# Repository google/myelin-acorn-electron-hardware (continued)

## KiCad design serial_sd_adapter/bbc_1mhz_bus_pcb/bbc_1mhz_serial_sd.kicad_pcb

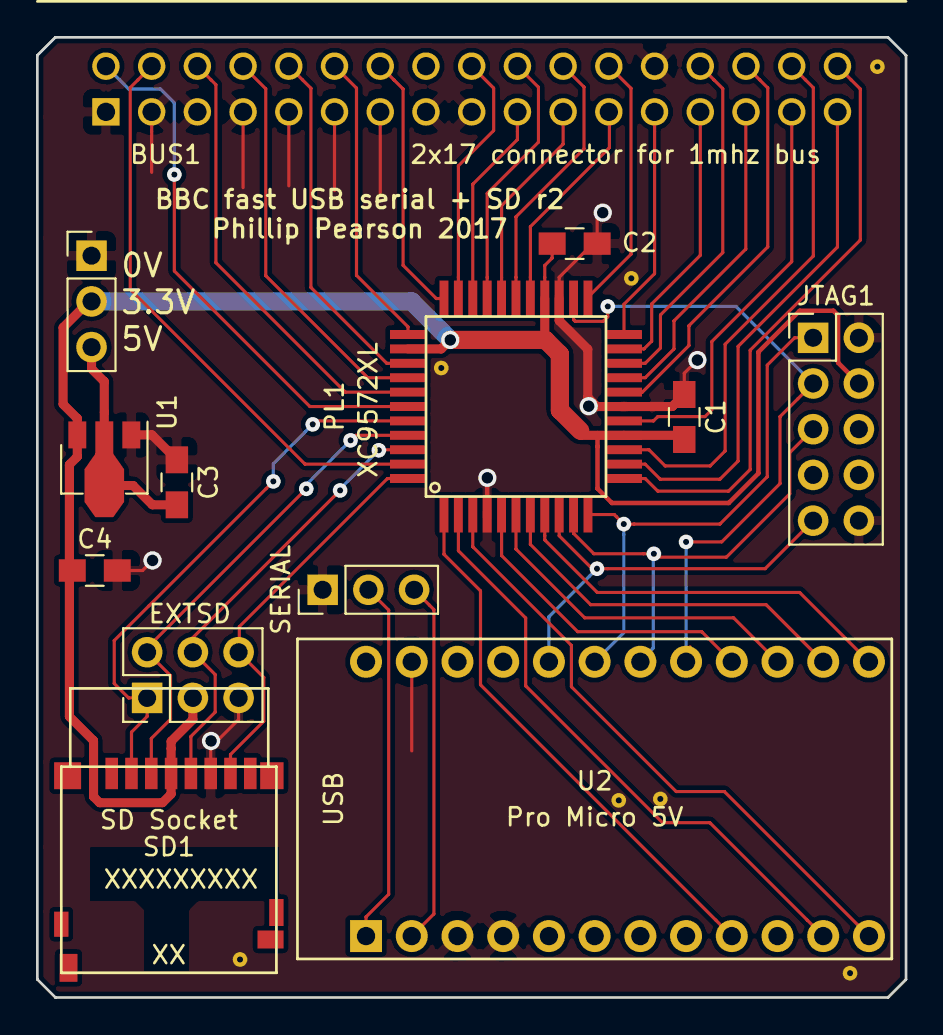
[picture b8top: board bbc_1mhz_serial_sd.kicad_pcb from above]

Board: 2 copper layers, 48.3 x 53.3 mm, 20 parts (0 on the bottom side), 43 nets.

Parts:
BUS1: 2x17 connector for 1mhz bus; bbc_1mhz_bus_board
C1, C2: 100n; C_0805_HandSoldering
C3, C4: 1u; C_0805_HandSoldering
EXTPWR: ext pwr; Pin_Header_Straight_1x03_Pitch2.54mm
EXTSD: ext sd; Pin_Header_Straight_2x03_Pitch2.54mm
JTAG1: jtag; Pin_Header_Straight_2x05_Pitch2.54mm
PL1: XC9572XL; xilinx_vqg44
SD1: SD Socket; hirose_micro_sd_card_socket
SERIAL: serial; Pin_Header_Straight_1x03_Pitch2.54mm
U1: MCP1700T-3302E/MB; SOT-89-3
U2: Pro Micro 5V; pro_micro
staple_single1, staple_single2, staple_single3, staple_single4, staple_single5, staple_single6, staple_single7: via_single

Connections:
3V3: C1.2, C2.1, C4.1, EXTPWR.2, EXTSD.3, JTAG1.4, PL1.15, PL1.26, PL1.35, SD1.4, U1.3
5V: C3.2, EXTPWR.3, U1.2
GND: BUS1.1, BUS1.3, BUS1.5, BUS1.7, BUS1.9, BUS1.11, BUS1.13, BUS1.15, BUS1.17, BUS1.26, C1.1, C2.2, C3.1, C4.2, EXTPWR.1, EXTSD.5, JTAG1.2, JTAG1.10, PL1.4, PL1.17, PL1.25, SD1.6, SERIAL.1, U1.1, U2.3, U2.4, U2.23, staple_single1.1, staple_single2.1, staple_single3.1, staple_single4.1, staple_single5.1, staple_single6.1, staple_single7.1
avr_INT: PL1.8, U2.13
avr_MISC1: PL1.1, U2.9
avr_MISO: PL1.6, U2.15
avr_MOSI: PL1.7, U2.14
avr_RXD: SERIAL.3, U2.2
avr_SCK: PL1.5, U2.16
avr_TXD: SERIAL.2, U2.1
avr_nSD_SEL: PL1.2, U2.11
avr_nSS: PL1.3, U2.12
bbc_1MHZE: BUS1.4, PL1.43
bbc_A0: BUS1.27, PL1.21
bbc_A1: BUS1.28, PL1.20
bbc_A2: BUS1.29, PL1.19
bbc_A3: BUS1.30, PL1.18
bbc_A4: BUS1.31, PL1.16
bbc_A5: BUS1.32, PL1.14
bbc_A6: BUS1.33, PL1.13
bbc_A7: BUS1.34, PL1.12
bbc_D0: BUS1.18, PL1.32
bbc_D1: BUS1.19, PL1.31
bbc_D2: BUS1.20, PL1.30
bbc_D3: BUS1.21, PL1.29
bbc_D4: BUS1.22, PL1.28
bbc_D5: BUS1.23, PL1.27
bbc_D6: BUS1.24, PL1.23
bbc_D7: BUS1.25, PL1.22
bbc_RnW: BUS1.2, PL1.39
bbc_nIRQ: BUS1.8, PL1.37
bbc_nNMI: BUS1.6, PL1.38
bbc_nPGFC: BUS1.10, PL1.36
bbc_nPGFD: BUS1.12, PL1.34
bbc_nRESET: BUS1.14, PL1.33
cpld_TCK: JTAG1.1, PL1.11, U2.19
cpld_TDI: JTAG1.9, PL1.9, U2.20
cpld_TDO: JTAG1.3, PL1.24, U2.17
cpld_TMS: JTAG1.5, PL1.10, U2.18
sd_MISO: EXTSD.6, PL1.44, SD1.7
sd_MOSI: EXTSD.2, PL1.41, SD1.3
sd_SCK: EXTSD.4, PL1.42, SD1.5
sd_nSS: EXTSD.1, PL1.40, SD1.2

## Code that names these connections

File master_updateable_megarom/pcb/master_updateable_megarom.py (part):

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        # we could wire flash_nCE low and ignore bbc_nCE.
        Pin(1,  "P2.10",   ["D6"]),
        Pin(2,  "GTS2",    ["D7"]),
        Pin(4,  "P2.12",   ["bbc_A0"]),
        Pin(5,  "GTS1",    ["bbc_A1"]),
        Pin(6,  "P2.15",   ["bbc_A2"]),
        Pin(7,  "P2.17",   ["bbc_A3"]),
        Pin(8,  "P1.2",    ["bbc_A10"]),
        Pin(9,  "P1.5",    ["bbc_A4"]),
        Pin(10, "P1.6",    ["bbc_A16"]),
        Pin(11, "P1.8",    ["bbc_A5"]),
        Pin(12, "P1.3",    ["bbc_A11"]),
        Pin(13, "P1.4",    ["bbc_A6"]),
        Pin(15, "P1.GCK1", ["bbc_A9"]),  # Should have put SCK on one of these!
        Pin(16, "P1.GCK2", ["bbc_A7"]),  # Try drilling out one of the tracks and
        Pin(17, "P1.GCK3", ["bbc_A8"]),  # using it as a spare GCK pin.
        Pin(18, "P1.10",   ["bbc_A12"]),
        Pin(19, "P1.15",   ["cpld_JP1"]),  # TODO(r2) shuffle pins around so
        Pin(20, "P1.17",   ["bbc_A15"]),   # cpld_SCK ends up on a GCK.
        Pin(22, "P3.2",    ["cpld_JP0"]),
        Pin(23, "P1.12",   ["bbc_A13"]),
        Pin(24, "P3.5",    ["bbc_A14"]),
        Pin(25, "P3.8",    ["cpld_MISO"]),
        Pin(27, "P3.9",    ["cpld_MOSI"]),
        Pin(31, "P3.3",    ["cpld_SCK"]),
        Pin(32, "P3.4",    ["cpld_SS"]),
        Pin(33, "P3.11",   ["flash_A0"]),
        Pin(34, "P3.6",    ["flash_A1"]),
        Pin(35, "P3.14",   ["flash_A2"]),
        Pin(36, "P3.15",   ["flash_A3"]),
        Pin(38, "P3.17",   ["flash_A4"]),
        Pin(39, "P3.10",   ["flash_A5"]),
        Pin(40, "P3.12",   ["flash_A6"]),
        Pin(42, "P3.16",   ["flash_A7"]),
        Pin(43, "P4.2",    ["flash_A12"]),
        Pin(44, "P4.5",    ["flash_A15"]),
        Pin(45, "P4.8",    ["flash_A16"]),
        Pin(46, "P4.3",    ["flash_A18"]),
        Pin(47, "P4.4",    ["flash_nWE"]),
        Pin(48, "P4.11",   ["flash_A17"]),
        Pin(49, "P4.6",    ["flash_A14"]),
        Pin(50, "P4.14",   ["flash_A13"]),
        Pin(51, "P4.10",   ["flash_A8"]),
        Pin(52, "P4.12",   ["flash_A9"]),
        Pin(56, "P4.15",   ["flash_A11"]),
        Pin(57, "P4.17",   ["flash_nOE"]),
        Pin(58, "P2.3",    ["flash_A10"]),
        Pin(59, "P2.4",    ["D0"]),
        Pin(60, "P2.2",    ["D2"]),
        Pin(61, "P2.5",    ["D3"]),
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        Pin(55, "VCCIO_2V5_3V3", ["3V3"]),

        # 4 JTAG programming interface pins
        Pin(28, "TDI", ["cpld_TDI"]),
        Pin(29, "TMS", ["cpld_TMS"]),
        Pin(30, "TCK", ["cpld_TCK"]),
        Pin(53, "TDO", ["cpld_TDO"]),
    ],
)
cpld_cap1 = myelin_kicad_pcb.C0805("100n", "3V3", "GND", ref="C1")
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    value="jtag",
    desc="2x5 header for JTAG programming.  Use generic 0.1 inch header strip or Digikey ED1543-ND.",
    pins=[
        Pin(1, "TCK", ["cpld_TCK"]), # top left
        Pin(2, "GND", ["GND"]), # top right
        Pin(3, "TDO", ["cpld_TDO"]),
        Pin(4, "3V3", ["3V3"]),
        Pin(5, "TMS", ["cpld_TMS"]),
        Pin(6, "NC"),
        Pin(7, "NC"),
        Pin(8, "NC"),
        Pin(9, "TDI", ["cpld_TDI"]),
        Pin(10, "GND", ["GND"]),
    ],
)
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    desc="1x3 0.1 inch male header",
    pins=[
        Pin(1, "GND", ["GND"]),
        Pin(2, "SCK", ["cpld_SCK"]),
        Pin(3, "nSS", ["cpld_SS"]),
        Pin(4, "MISO", ["cpld_MOSI"]),
        Pin(5, "MOSI", ["cpld_MISO"]),
    ],
)

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    desc="1x4 0.1 inch male header",
    pins=[
        Pin(1, "GND", ["GND"]),
        Pin(2, "JP0", ["cpld_JP0"]),
        Pin(3, "JP1", ["cpld_JP1"]),
        Pin(4, "3V3", ["5V"]),
    ],
)
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    value="SST39SF010A/020A/040",
    desc="128kB/256kB/512kB flash chip in SST 'NH' PLCC-32 package: SST39SF040-XX-XX-NHE, SST39SF020A-XX-XX-NHE, or SST39SF010A-XX-XX-NHE",
    pins=[
        Pin(1, "A18",  ["flash_A18"]),
        Pin(2, "A16",  ["flash_A16"]),
        Pin(3, "A15",  ["flash_A15"]),
        Pin(4, "A12",  ["flash_A12"]),
        Pin(5, "A7",   ["flash_A7"]),
        Pin(6, "A6",   ["flash_A6"]),
        Pin(7, "A5",   ["flash_A5"]),
        Pin(8, "A4",   ["flash_A4"]),
        Pin(9, "A3",   ["flash_A3"]),
        Pin(10, "A2",  ["flash_A2"]),
        Pin(11, "A1",  ["flash_A1"]),
        Pin(12, "A0",  ["flash_A0"]),
        Pin(13, "D0",  ["D0"]),
        Pin(14, "D1",  ["D1"]),
        Pin(15, "D2",  ["D2"]),
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        Pin(20, "D6",  ["D6"]),
        Pin(21, "D7",  ["D7"]),
        Pin(22, "nCE", ["GND"]),  # flash chip permanently enabled
        Pin(23, "A10", ["flash_A10"]),
        Pin(24, "nOE", ["flash_nOE"]),
        Pin(25, "A11", ["flash_A11"]),
        Pin(26, "A9",  ["flash_A9"]),
        Pin(27, "A8",  ["flash_A8"]),
        Pin(28, "A13", ["flash_A13"]),
        Pin(29, "A14", ["flash_A14"]),
        Pin(30, "A17", ["flash_A17"]),
        Pin(31, "nWE", ["flash_nWE"]),
        Pin(32, "VDD", ["5V"]),
    ],
)
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    value="MOS ROM",
    desc="Adapter to emulate a 600mil 28-pin DIP, e.g. Digikey 1175-1525-5-ND",
    pins=[
        Pin( "1", "A15", ["bbc_A15"]),
        Pin( "2", "A12", ["bbc_A12"]),
        Pin( "3", "A7",  ["bbc_A7"]),
        Pin( "4", "A6",  ["bbc_A6"]),
        Pin( "5", "A5",  ["bbc_A5"]),
        Pin( "6", "A4",  ["bbc_A4"]),
        Pin( "7", "A3",  ["bbc_A3"]),
        Pin( "8", "A2",  ["bbc_A2"]),
        Pin( "9", "A1",  ["bbc_A1"]),
        Pin("10", "A0",  ["bbc_A0"]),
        Pin("11", "D0",  ["D0"]),
        Pin("12", "D1",  ["D1"]),
        Pin("13", "D2",  ["D2"]),
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        Pin("17", "D5",  ["D5"]),
        Pin("18", "D6",  ["D6"]),
        Pin("19", "D7",  ["D7"]),
        Pin("20", "nCS", ),  # bbc /CS ignored because it's tied to GND on the motherboard
        Pin("21", "A10", ["bbc_A10"]),
        Pin("22", "A16", ["bbc_A16"]),
        Pin("23", "A11", ["bbc_A11"]),
        Pin("24", "A9",  ["bbc_A9"]),
        Pin("25", "A8",  ["bbc_A8"]),
        Pin("26", "A13", ["bbc_A13"]),
        Pin("27", "A14", ["bbc_A14"]),
        Pin("28", "VCC", ["5V"]),
    ],
)
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#     value="74LVC245",
#     pins=[
#         Pin( 1, "A->B", ["abuf_ext_to_cpu"]),
#         Pin( 2, "A0", ["ext_A0"]),
#         Pin( 3, "A1", ["ext_A1"]),
#         Pin( 4, "A2", ["ext_A2"]),
#         Pin( 5, "A3", ["ext_A3"]),
#         Pin( 6, "A4", ["ext_A4"]),
#         Pin( 7, "A5", ["ext_A5"]),
#         Pin( 8, "A6", ["ext_A6"]),
#         Pin( 9, "A7", ["ext_A7"]),
#         Pin(10, "GND", ["GND"]),
#         Pin(11, "B7", ["cpu_A7"]),
#         Pin(12, "B6", ["cpu_A6"]),
#         Pin(13, "B5", ["cpu_A5"]),
#         Pin(14, "B4", ["cpu_A4"]),
#         Pin(15, "B3", ["cpu_A3"]),
#         Pin(16, "B2", ["cpu_A2"]),
#         Pin(17, "B1", ["cpu_A1"]),
#         Pin(18, "B0", ["cpu_A0"]),
#         Pin(19, "nCE", ["abuf_nCE"]),
#         Pin(20, "VCC", ["3V3"]),
#     ],
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#     value="74LVC245",
#     pins=[
#         Pin( 1, "A->B", ["abuf_ext_to_cpu"]),
#         Pin( 2, "A0", ["ext_A8"]),
#         Pin( 3, "A1", ["ext_A9"]),
#         Pin( 4, "A2", ["ext_A10"]),
#         Pin( 5, "A3", ["ext_A11"]),
#         Pin( 6, "A4", ["ext_A12"]),
#         Pin( 7, "A5", ["ext_A13"]),
#         Pin( 8, "A6", ["ext_A14"]),
#         Pin( 9, "A7", ["ext_A15"]),
#         Pin(10, "GND", ["GND"]),
#         Pin(11, "B7", ["cpu_A15_2"]),
#         Pin(12, "B6", ["cpu_A14_2"]),
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#         Pin(29, "P0.5",   [""]),
#         Pin(30, "P0.6",   [""]),
#         Pin(31, "P0.7",   [""]),
#         Pin(32, "nRESET", ["mcu_nreset"]),
#         Pin(33, "VCCD",   ["mcu_vccd"]),  # regulated supply; connect to 1uF cap or 1.8V
#         Pin(34, "VDDD",   ["5V"]),
#         Pin(35, "VDDA",   ["5V"]),
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
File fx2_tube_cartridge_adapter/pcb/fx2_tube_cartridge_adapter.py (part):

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        # front of cartridge / bottom layer of PCB
        Pin( "B1", "5V",    "5V"),
        Pin( "B2", "A10"),
        Pin( "B3", "D3",    "cpu_D3"),
        Pin( "B4", "A11"),
        Pin( "B5", "A9"),
        Pin( "B6", "D7",    "cpu_D7"),
        Pin( "B7", "D6",    "cpu_D6"),
        Pin( "B8", "D5",    "cpu_D5"),
        Pin( "B9", "D4",    "cpu_D4"),
        Pin("B10", "nOE2"),
        Pin("B11", "BA7",   "cpu_A7"),
        Pin("B12", "BA6",   "cpu_A6"),
        Pin("B13", "BA5",   "cpu_A5"),
        Pin("B14", "BA4",   "cpu_A4"),
        Pin("B15", "BA3",   "cpu_A3"),
        Pin("B16", "BA2",   "cpu_A2"),
        Pin("B17", "BA1",   "cpu_A1"),
        Pin("B18", "BA0",   "cpu_A0"),
        Pin("B19", "D0",    "cpu_D0"),
        Pin("B20", "D2",    "cpu_D2"),
        Pin("B21", "D1",    "cpu_D1"),
        Pin("B22", "GND",   "GND"),
        # rear of cartridge / top layer of PCB
        Pin( "A1", "5V",    "5V"),
        Pin( "A2", "nOE"),
        Pin( "A3", "nRST",  "cpu_nRST"),
        # A4 is RnW on the Elk, and on the master for &FCxx, so it's safe to use
        # this for the Tube, but not for the logic analyzer.
        Pin( "A4", "RnW",   "cpu_RnW"),
        Pin( "A5", "A8"),
        Pin( "A6", "A13"),
        Pin( "A7", "A12"),
        Pin( "A8", "PHI0",  "cpu_CLK"),
        Pin( "A9", "-5V"),
        Pin("A10", "NC"),
        Pin("A11", "READY", "elk_READY_master_RnW"),
        Pin("A12", "nNMI",  "cpu_nNMI"),
        Pin("A13", "nIRQ",  "cpu_nIRQ"),
        Pin("A14", "nINFC", "elk_nINFC"),
        Pin("A15", "nINFD"),
        Pin("A16", "ROMQA"),
        Pin("A17", "16MHZ", "elk_16MHz"),
        Pin("A18", "nROMSTB"),
        Pin("A19", "ADOUT"),
        Pin("A20", "ADGND"),
        Pin("A21", "ADIN"),
        Pin("A22", "GND",   "GND"),
    ],
)
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    value="tube",
    pins=[
        Pin( 1, "0V", "GND"),
        Pin( 2, "RnW", "cpu_RnW"),
        Pin( 3, "0V", "GND"),
        Pin( 4, "2MHzE", "cpu_CLK"),
        Pin( 5, "0V", "GND"),
        Pin( 6, "/IRQ", "cpu_nIRQ"),
        Pin( 7, "0V", "GND"),
        Pin( 8, "/TUBE", "bbc_nTUBE"),
        Pin( 9, "0V", "GND"),
        Pin(10, "/RST", "cpu_nRST"),
        Pin(11, "0V", "GND"),
        Pin(12, "D0", "cpu_D0"),
        Pin(13, "0V", "GND"),
        Pin(14, "D1", "cpu_D1"),
        Pin(15, "0V", "GND"),
        Pin(16, "D2", "cpu_D2"),
        Pin(17, "0V", "GND"),
        Pin(18, "D3", "cpu_D3"),
        Pin(19, "0V", "GND"),
        Pin(20, "D4", "cpu_D4"),
        Pin(21, "0V", "GND"),
        Pin(22, "D5", "cpu_D5"),
        Pin(23, "0V", "GND"),
        Pin(24, "D6", "cpu_D6"),
        Pin(25, "0V", "GND"),
        Pin(26, "D7", "cpu_D7"),
        Pin(27, "0V", "GND"),
        Pin(28, "A0", "cpu_A0"),
        Pin(29, "0V", "GND"),
        Pin(30, "A1", "cpu_A1"),
        Pin(31, "+5V", "5V"),
        Pin(32, "A2", "cpu_A2"),
        Pin(33, "+5V", "5V"),
        Pin(34, "A3", "cpu_A3"),
        Pin(35, "+5V", "5V"),
        Pin(36, "A4", "cpu_A4"),
        Pin(37, "+5V", "5V"),
        Pin(38, "A5", "cpu_A5"),
        Pin(39, "+5V", "5V"),
        Pin(40, "A6", "cpu_A6"),
    ],
)

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    value="XC9572XL",
    buses=["cpu_D", "tube_D"],
    pins=[
        Pin(39, "P1.2", "cpu_D4"),
        Pin(40, "P1.5", "cpu_D5"),
        Pin(41, "P1.6", "cpu_D6"),
        Pin(42, "P1.8", "elk_nINFC"),
        Pin(43, "P1.9-GCK1", "cpu_D7"),
        Pin(44, "P1.11-GCK2", "cpu_A0"),
        Pin( 1, "P1.14-GCK3", "elk_16MHz"),
        Pin( 2, "P1.15", "cpu_A1"),
        Pin( 3, "P1.17", "cpu_A2"),
        Pin( 4, "GND", "GND"),
        Pin( 5, "P3.2", "cpu_A4"),
        Pin( 6, "P3.5", "cpu_A5"),
        Pin( 7, "P3.8", "cpu_A6"),
        Pin( 8, "P3.9", "tube_CLK"),
        Pin( 9, "TDI", "cpld_TDI"),
        Pin(10, "TMS", "cpld_TMS"),
        Pin(11, "TCK", "cpld_TCK"),
        Pin(12, "P3.11", "tube_D0"),
        Pin(13, "P3.14", "tube_D3"),
        Pin(14, "P3.15", "tube_D1"),
        Pin(15, "VCCINT_3V3", "3V3"),
        Pin(16, "P3.17", "tube_D7"),
        Pin(17, "GND", "GND"),
        Pin(18, "P3.16", "tube_D2"),
        Pin(19, "P4.2", "tube_D6"),
        Pin(20, "P4.5", "tube_D4"),
        Pin(21, "P4.8", "tube_D5"),
        Pin(22, "P4.11", "tube_A0"),
        Pin(23, "P4.14", "tube_nTUBE"),
        Pin(24, "TDO", "cpld_TDO"),
        Pin(25, "GND", "GND"),
        Pin(26, "VCCIO_2V5_3V3", "3V3"),
        Pin(27, "P4.15", "tube_RnW"),
        Pin(28, "P4.17", "tube_A2"),
        Pin(29, "P2.2", "tube_A1"),
        Pin(30, "P2.5", "cpu_RnW"),
        Pin(31, "P2.6", "cpu_CLK"),
        Pin(32, "P2.8", "bbc_nTUBE"),
        Pin(33, "P2.9-GSR", "cpu_D0"),
        Pin(34, "P2.11-GTS2", "cpu_D1"),
        Pin(35, "VCCINT_3V3", "3V3"),
        Pin(36, "P2.14-GTS1", "cpu_A7"),
        Pin(37, "P2.15", "cpu_D2"),
        Pin(38, "P2.17", "cpu_D3"),
    ],
)
cpld_cap1 = myelin_kicad_pcb.C0805("100n", "3V3", "GND", ref="C1", handsoldering=False)
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	pins=[
		Pin(1, "3V3", "3V3_PI"),  # for when we want the Pi to power the CPLD
		Pin(2, "5V"),
		Pin(3, "GPIO0-2", ["tube_A1"]),
		Pin(4, "5V"),
		Pin(5, "GPIO1-3", ["tube_A2"]),
		Pin(6, "ser_GND", ["pi_serial_GND"]),
		Pin(7, "GPIO4", ["tube_nRST"]),
		Pin(8, "ser_TX", ["pi_serial_TX"]),
		Pin(9, "GND", ["GND"]),
		Pin(10, "ser_RX", ["pi_serial_RX"]),
		Pin(11, "GPIO17", ["tube_nTUBE"]),
		Pin(12, "GPIO18", ["tube_RnW"]),
		Pin(13, "GPIO21-27", ["tube_A0"]),
		Pin(14, "GND", ["GND"]),
		Pin(15, "GPIO22", ["tube_D4"]),
		Pin(16, "GPIO23", ["tube_D5"]),
		Pin(17, "3V3"),
		Pin(18, "GPIO24", ["tube_D6"]),
		Pin(19, "GPIO10", ["tube_D2"]),
		Pin(20, "GND", ["GND"]),
		Pin(21, "GPIO9", ["tube_D1"]),
		Pin(22, "GPIO25", ["tube_D7"]),
		Pin(23, "GPIO11", ["tube_D3"]),
		Pin(24, "GPIO8", ["tube_D0"]),
		Pin(25, "GND", ["GND"]),
		Pin(26, "GPIO7", ["tube_CLK"]),
	],
)

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	identifier="SERIAL1",  # TODO(r2) rename to SERIAL
	value="Pi Serial",
	pins=[
		Pin(1, "GND", ["pi_serial_GND"]),
		Pin(2, "TX", ["pi_serial_TX"]),
		Pin(3, "RX", ["pi_serial_RX"]),
	],
)

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    identifier="JTAG1",  # TODO(r2) rename to JTAG
    value="jtag",
    pins=[
        Pin(1, "TCK", ["cpld_TCK"]), # top left
        Pin(2, "GND", ["GND"]), # top right
        Pin(3, "TDO", ["cpld_TDO"]),
        Pin(4, "3V3", ["3V3"]),
        Pin(5, "TMS", ["cpld_TMS"]),
        Pin(6, "NC"),
        Pin(7, "NC"),
        Pin(8, "NC"),
        Pin(9, "TDI", ["cpld_TDI"]),
        Pin(10, "GND", ["GND"]),
    ],
)
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    pins=[
        # left side, top to bottom, left to right, with board face up
        # and USB socket upward
        Pin( "L1", "PD5", "cpu_nNMI"),  # DONE add header for BBC test clip
        Pin( "L2", "PD6", "cpu_nRST"),
        Pin( "L3", "PD7", "tube_A0"),
        Pin( "L4", "GND", "GND"),
        Pin( "L5", "CLK"),
        Pin( "L6", "GND", "GND"),
        Pin( "L7", "RDY0", "analyzer_RDY0"),  # tie to 3V3 via 1k resistor
        Pin( "L8", "RDY1", "tube_CLK_jumper"),  # via jumper to tube_CLK
        Pin( "L9", "GND", "GND"),
        Pin("L10", "GND", "GND"),
        Pin("L11", "GND", "GND"),
        Pin("L12", "FCLK"),
        Pin("L13", "SCL"),
        Pin("L14", "SDA"),
        Pin("L15", "PB0", "tube_D0"),
        Pin("L16", "PB1", "tube_D1"),
        Pin("L17", "PB2", "tube_D2"),
        Pin("L18", "PB3", "tube_D3"),
        Pin("L19", "3V3", "3V3_FX2"),  # generated from USB
        Pin("L20", "3V3", "3V3_FX2"),  # generated from USB

        # right side, top to bottom, left to right
        Pin( "R1", "PD4", "cpu_nIRQ"),
        Pin( "R2", "PD3", "tube_CLK"),
        Pin( "R3", "PD2", "analyzer_PD2_READY"),  # DONE add header for BBC test clip
        Pin( "R4", "PD1", "cpu_SYNC"),  # DONE add header for test clip
        Pin( "R5", "PD0", "analyzer_PD0_RnW"),  # DONE add header to switch Elk pin A4/Master pin A11
        Pin( "R6", "PA7"),
        Pin( "R7", "PA6", "analyzer_PA6"),  # tie to 3V3 via 1k resistor
        Pin( "R8", "PA5", "analyzer_PA5"),  # tie to 3V3 via 1k resistor
        Pin( "R9", "PA4", "analyzer_PA4"),  # tie to GND via 1k resistor
        Pin("R10", "PA3"),
        Pin("R11", "PA2", "analyzer_PA2"),  # tie to 3V3 via 1k resistor
        Pin("R12", "PA1"),
        Pin("R13", "PA0"),
        Pin("R14", "CTL2"),
        Pin("R15", "CTL1"),
        Pin("R16", "CTL0"),
        Pin("R17", "PB7", "tube_D7"),
        Pin("R18", "PB6", "tube_D6"),
        Pin("R19", "PB5", "tube_D5"),
        Pin("R20", "PB4", "tube_D4"),
    ],
)
pull_resistors = [
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# Master: test clip for READY, elk_READY_master_RnW, cpu_nNMI, test clip for SYNC

# L8: capture clock
# L1/PD5/nNMI: 1-pin header (already connected for Elk/Master)
# R4/PD1/SYNC: 1-pin header
# R3/PD2/READY 2-pin header: bridge for Elk, add lead for everyone else
#   [PD2] [elk_READY_master_RnW]
# R5/PD0/RnW: 3-pin header: bridge left for Elk/Beeb, up for Master
#   [tube_RnW] [PD0]

sync_clk_jumper = myelin_kicad_pcb.Component(
	footprint="Pin_Headers:Pin_Header_Straight_2x04_Pitch2.54mm",
	identifier="LEADS",  # TODO(r2) rename to OPTS
	value="Options",
	pins=[
		Pin(1, "", "tube_CLK"),
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
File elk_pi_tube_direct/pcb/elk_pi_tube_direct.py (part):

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    value="edge connector",
    pins=[
        # front of cartridge / bottom layer of PCB
        Pin("B1", "5V", ["elk_5V"]),
        Pin("B2", "A10"),
        Pin("B3", "D3", ["elk_D3"]),
        Pin("B4", "A11"),
        Pin("B5", "A9"),
        Pin("B6", "D7", ["elk_D7"]),
        Pin("B7", "D6", ["elk_D6"]),
        Pin("B8", "D5", ["elk_D5"]),
        Pin("B9", "D4", ["elk_D4"]),
        Pin("B10", "nOE2"),
        Pin("B11", "BA7", ["elk_A7"]),
        Pin("B12", "BA6", ["elk_A6"]),
        Pin("B13", "BA5", ["elk_A5"]),
        Pin("B14", "BA4", ["elk_A4"]),
        Pin("B15", "BA3"),
        Pin("B16", "BA2", ["elk_A2"]),
        Pin("B17", "BA1", ["elk_A1"]),
        Pin("B18", "BA0", ["elk_A0"]),
        Pin("B19", "D0", ["elk_D0"]),
        Pin("B20", "D2", ["elk_D2"]),
        Pin("B21", "D1", ["elk_D1"]),
        Pin("B22", "GND", ["GND"]),
        # rear of cartridge / top layer of PCB
        Pin("A1", "5V", ["elk_5V"]),
        Pin("A2", "nOE"),
        Pin("A3", "nRST", ["elk_nRST"]),
        Pin("A4", "RnW", ["elk_RnW"]),
        Pin("A5", "A8"),
        Pin("A6", "A13"),
        Pin("A7", "A12"),
        Pin("A8", "PHI0", ["elk_PHI0"]),
        Pin("A9", "-5V"),
        Pin("A10", "NC"),
        Pin("A11", "nRDY"),
        Pin("A12", "nNMI"),
        Pin("A13", "nIRQ"),
        Pin("A14", "nINFC", ["elk_nINFC"]),
        Pin("A15", "nINFD"),
        Pin("A16", "ROMQA"),
        Pin("A17", "16MHZ"),
        Pin("A18", "nROMSTB"),
        Pin("A19", "ADOUT"),
        Pin("A20", "ADGND"),
        Pin("A21", "ADIN"),
        Pin("A22", "GND", ["GND"]),
    ],
)
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	pins=[
		Pin(1, "3V3", ["3V3"]),
		Pin(2, "5V", ["5V"]),
		Pin(3, "GPIO0-2", ["tube_A1"]),
		Pin(4, "5V", ["5V"]),
		Pin(5, "GPIO1-3", ["tube_A2"]),
		Pin(6, "ser_GND", ["pi_serial_GND"]),
		Pin(7, "GPIO4", ["tube_nRST"]),
		Pin(8, "ser_TX", ["pi_serial_TX"]),
		Pin(9, "GND", ["GND"]),
		Pin(10, "ser_RX", ["pi_serial_RX"]),
		Pin(11, "GPIO17", ["tube_nTUBE"]),
		Pin(12, "GPIO18", ["tube_RnW"]),
		Pin(13, "GPIO21-27", ["tube_A0"]),
		Pin(14, "GND", ["GND"]),
		Pin(15, "GPIO22", ["tube_D4"]),
		Pin(16, "GPIO23", ["tube_D5"]),
		Pin(17, "3V3", ["3V3"]),
		Pin(18, "GPIO24", ["tube_D6"]),
		Pin(19, "GPIO10", ["tube_D2"]),
		Pin(20, "GND", ["GND"]),
		Pin(21, "GPIO9", ["tube_D1"]),
		Pin(22, "GPIO25", ["tube_D7"]),
		Pin(23, "GPIO11", ["tube_D3"]),
		Pin(24, "GPIO8", ["tube_D0"]),
		Pin(25, "GND", ["GND"]),
		Pin(26, "GPIO7", ["tube_PHI0"]),
	],
)

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	identifier="SERIAL1",
	value="Pi Serial",
	pins=[
		Pin(1, "GND", ["pi_serial_GND"]),
		Pin(2, "TX", ["pi_serial_TX"]),
		Pin(3, "RX", ["pi_serial_RX"]),
	],
)

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    footprint="myelin-kicad:xilinx_vqg44",
    identifier="PL1",
    value="XC9572XL",
    # Prefixes used by update_xilinx_constraints to turn pin names like elk_D0 into
    # signal IDs like elk_D<0> in constraints.ucf:
    buses=["elk_D", "tube_D"],
    pins=[
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        # ninfc brown
        # rnw red

        # NET LED2 LOC = P34; # tube_RnW
        # NET LED3 LOC = P33; # tube_nTUBE
        # NET LED4 LOC = P32; # tube_A0
        # NET LED5 LOC = P31; # tube_D5

        Pin(39, "P1.2", ["elk_D3"]),
        Pin(40, "P1.5", ["elk_nRST"]),
        Pin(41, "P1.6", ["elk_RnW"]),
        Pin(42, "P1.8", ["elk_D7"]),
        Pin(43, "P1.9-GCK1", ["elk_D6"]),
        Pin(44, "P1.11-GCK2", ["elk_D5"]),
        Pin(1, "P1.14-GCK3", ["elk_PHI0"]),
        Pin(2, "P1.15", ["elk_D4"]),
        Pin(3, "P1.17", ["elk_A7"]),
        Pin(4, "GND", ["GND"]),
        Pin(5, "P3.2", ["elk_A6"]),
        Pin(6, "P3.5", ["elk_A5"]),
        Pin(7, "P3.8", ["elk_A4"]),
        Pin(8, "P3.9", ["elk_nINFC"]),
        Pin(9, "TDI", ["cpld_TDI"]),
        Pin(10, "TMS", ["cpld_TMS"]),
        Pin(11, "TCK", ["cpld_TCK"]),
        Pin(12, "P3.11", ["elk_A2"]),
        Pin(13, "P3.14", ["elk_A1"]),
        Pin(14, "P3.15", ["elk_A0"]),
        Pin(15, "VCCINT_3V3", ["3V3"]),
        Pin(16, "P3.17", ["elk_D0"]),
        Pin(17, "GND", ["GND"]),
        Pin(18, "P3.16", ["elk_D2"]),
        Pin(19, "P4.2", ["elk_D1"]),
        Pin(20, "P4.5", ["tube_PHI0"]),
        Pin(21, "P4.8", ["tube_D3"]),
        Pin(22, "P4.11", ["tube_D0"]),
        Pin(23, "P4.14", ["tube_D1"]),
        Pin(24, "TDO", ["cpld_TDO"]),
        Pin(25, "GND", ["GND"]),
        Pin(26, "VCCIO_2V5_3V3", ["3V3"]),
        Pin(27, "P4.15", ["tube_D7"]),
        Pin(28, "P4.17", ["tube_D2"]),
        Pin(29, "P2.2", ["tube_D6"]),
        Pin(30, "P2.5", ["tube_D4"]),
        Pin(31, "P2.6", ["tube_D5"]),
        Pin(32, "P2.8", ["tube_A0"]),
        Pin(33, "P2.9-GSR", ["tube_nTUBE"]),
        Pin(34, "P2.11-GTS2", ["tube_RnW"]),
        Pin(35, "VCCINT_3V3", ["3V3"]),
        Pin(36, "P2.14-GTS1", ["tube_nRST"]),
        Pin(37, "P2.15", ["tube_A2"]),
        Pin(38, "P2.17", ["tube_A1"]),
    ],
)
cpld_cap1 = myelin_kicad_pcb.C0805("100n", "3V3", "GND", ref="C1")
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    identifier="JTAG1",
    value="jtag",
    pins=[
        Pin(1, "TCK", ["cpld_TCK"]), # top left
        Pin(2, "GND", ["GND"]), # top right
        Pin(3, "TDO", ["cpld_TDO"]),
        Pin(4, "3V3", ["3V3"]),
        Pin(5, "TMS", ["cpld_TMS"]),
        Pin(6, "NC"),
        Pin(7, "NC"),
        Pin(8, "NC"),
        Pin(9, "TDI", ["cpld_TDI"]),
        Pin(10, "GND", ["GND"]),
    ],
)
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    value="Elk-Pi 5V",
    pins=[
        Pin(1, "A", ["5V"]),
        Pin(2, "B", ["elk_5V"]),
    ],
)

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
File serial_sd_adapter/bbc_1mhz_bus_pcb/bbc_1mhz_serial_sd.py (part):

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        # want a pure GPIO board.

        Pin("1", "GND", ["GND"]),
        Pin("2", "RnW", ["bbc_RnW"]),
        Pin("3", "GND", ["GND"]),
        Pin("4", "1MHZE", ["bbc_1MHZE"]),
        Pin("5", "GND", ["GND"]),
        Pin("6", "nNMI", ["bbc_nNMI"]),
        Pin("7", "GND", ["GND"]),
        Pin("8", "nIRQ", ["bbc_nIRQ"]),
        Pin("9", "GND", ["GND"]),
        Pin("10", "nPGFC", ["bbc_nPGFC"]),
        Pin("11", "GND", ["GND"]),
        Pin("12", "nPGFD", ["bbc_nPGFD"]),
        Pin("13", "GND", ["GND"]),
        Pin("14", "nRESET", ["bbc_nRESET"]),
        Pin("15", "GND", ["GND"]),
        Pin("16", "AUDIO_IN_OUT"),
        Pin("17", "GND", ["GND"]),
        Pin("18", "D0", ["bbc_D0"]),
        Pin("19", "D1", ["bbc_D1"]),
        Pin("20", "D2", ["bbc_D2"]),
        Pin("21", "D3", ["bbc_D3"]),
        Pin("22", "D4", ["bbc_D4"]),
        Pin("23", "D5", ["bbc_D5"]),
        Pin("24", "D6", ["bbc_D6"]),
        Pin("25", "D7", ["bbc_D7"]),
        Pin("26", "GND", ["GND"]),
        Pin("27", "A0", ["bbc_A0"]),
        Pin("28", "A1", ["bbc_A1"]),
        Pin("29", "A2", ["bbc_A2"]),
        Pin("30", "A3", ["bbc_A3"]),
        Pin("31", "A4", ["bbc_A4"]),
        Pin("32", "A5", ["bbc_A5"]),
        Pin("33", "A6", ["bbc_A6"]),
        Pin("34", "A7", ["bbc_A7"]),
    ],
)

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    footprint="myelin-kicad:xilinx_vqg44",
    identifier="PL1",
    value="XC9572XL",
    # Prefixes used by update_xilinx_constraints to turn pin names like elk_D0 into
    # signal IDs like elk_D<0> in constraints.ucf:
    buses=["bbc_D", "bbc_A"],
    pins=[
        Pin(39, "P1.2", ["bbc_RnW"]),
        Pin(40, "P1.5", ["sd_nSS"]),
        Pin(41, "P1.6", ["sd_MOSI"]),
        Pin(42, "P1.8", ["sd_SCK"]),
        Pin(43, "P1.9-GCK1", ["bbc_1MHZE"]),
        Pin(44, "P1.11-GCK2", ["sd_MISO"]),
        Pin(1, "P1.14-GCK3", ["avr_MISC1"]),
        Pin(2, "P1.15", ["avr_nSD_SEL"]),
        Pin(3, "P1.17", ["avr_nSS"]),
        Pin(4, "GND", ["GND"]),
        Pin(5, "P3.2", ["avr_SCK"]),
        Pin(6, "P3.5", ["avr_MISO"]),
        Pin(7, "P3.8", ["avr_MOSI"]),
        Pin(8, "P3.9", ["avr_INT"]),
        Pin(9, "TDI", ["cpld_TDI"]),
        Pin(10, "TMS", ["cpld_TMS"]),
        Pin(11, "TCK", ["cpld_TCK"]),
        Pin(12, "P3.11", ["bbc_A7"]),
        Pin(13, "P3.14", ["bbc_A6"]),
        Pin(14, "P3.15", ["bbc_A5"]),
        Pin(15, "VCCINT_3V3", ["3V3"]),
        Pin(16, "P3.17", ["bbc_A4"]),
        Pin(17, "GND", ["GND"]),
        Pin(18, "P3.16", ["bbc_A3"]),
        Pin(19, "P4.2", ["bbc_A2"]),
        Pin(20, "P4.5", ["bbc_A1"]),
        Pin(21, "P4.8", ["bbc_A0"]),
        Pin(22, "P4.11", ["bbc_D7"]),
        Pin(23, "P4.14", ["bbc_D6"]),
        Pin(24, "TDO", ["cpld_TDO"]),
        Pin(25, "GND", ["GND"]),
        Pin(26, "VCCIO_2V5_3V3", ["3V3"]),
        Pin(27, "P4.15", ["bbc_D5"]),
        Pin(28, "P4.17", ["bbc_D4"]),
        Pin(29, "P2.2", ["bbc_D3"]),
        Pin(30, "P2.5", ["bbc_D2"]),
        Pin(31, "P2.6", ["bbc_D1"]),
        Pin(32, "P2.8", ["bbc_D0"]),
        Pin(33, "P2.9-GSR", ["bbc_nRESET"]),
        Pin(34, "P2.11-GTS2", ["bbc_nPGFD"]),
        Pin(35, "VCCINT_3V3", ["3V3"]),
        Pin(36, "P2.14-GTS1", ["bbc_nPGFC"]),
        Pin(37, "P2.15", ["bbc_nIRQ"]),
        Pin(38, "P2.17", ["bbc_nNMI"]),
    ],
)
cpld_cap1 = myelin_kicad_pcb.C0805("100n", "GND", "3V3", ref="C1")
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    identifier="JTAG1",
    value="jtag",
    pins=[
        Pin(1, "TCK", ["cpld_TCK"]), # top left
        Pin(2, "GND", ["GND"]), # top right
        Pin(3, "TDO", ["cpld_TDO"]),
        Pin(4, "3V3", ["3V3"]),
        Pin(5, "TMS", ["cpld_TMS"]),
        Pin(6, "NC"),
        Pin(7, "NC"),
        Pin(8, "NC"),
        Pin(9, "TDI", ["cpld_TDI"]),
        Pin(10, "GND", ["GND"]),
    ],
)
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    value="serial",
    pins=[
        Pin(1, "GND", ["GND"]),
        Pin(2, "TX", ["avr_TXD"]),
        Pin(3, "RX", ["avr_RXD"]),
    ],
)

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    value="Pro Micro 5V",
    pins=[
        # two rows of 12 pins, counter clockwise with pin 1 at top left
        Pin(1, "D1_TX_PD3", ["avr_TXD"]),
        Pin(2, "D0_RX_PD2", ["avr_RXD"]),
        Pin(3, "GND", ["GND"]),
        Pin(4, "GND", ["GND"]),
        Pin(5, "D2_SDA_PD1"),
        Pin(6, "D3_SCL_OC0B_PD0",),
        Pin(7, "D4_A6_PD4"),
        Pin(8, "D5_nOC4A_PC6"),
        Pin(9, "D6_A7_OC4D_PD7", ["avr_MISC1"]),
        Pin(10, "D7_PE6"),
        Pin(11, "D8_A8_PB4", ["avr_nSD_SEL"]),
        Pin(12, "D9_A9_nOC4B_PB5", ["avr_nSS"]), # pull this one up
        Pin(13, "D10_A10_OC4B_PB6", ["avr_INT"]),
        Pin(14, "D16_MOSI_PB2", ["avr_MOSI"]),
        Pin(15, "D14_MISO_PB3", ["avr_MISO"]),
        Pin(16, "D15_SCK_PB1", ["avr_SCK"]),
        Pin(17, "D18_A0_PF7", ["cpld_TDO"]),
        Pin(18, "D19_A1_PF6", ["cpld_TMS"]),
        Pin(19, "D20_A2_PF5", ["cpld_TCK"]),
        Pin(20, "D21_A3_PF4", ["cpld_TDI"]),
        Pin(21, "VCC"), # NC - power supplied by the board
        Pin(22, "RST"),
        Pin(23, "GND", ["GND"]),
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    pins=[
        # Pin("WP", "WP"),  # full size SD only
        Pin(8, "DAT1"),
        Pin(7, "DAT0_MISO", ["sd_MISO"]),
        Pin(6, "VSS", ["GND"]),
        Pin(5, "CLK_SCK", ["sd_SCK"]),
        Pin(4, "VDD", ["3V3"]),
        # Pin(3, "VSS"),  # full size SD only
        # Pin("CD", "CD"),  # full size SD only
        Pin(3, "CMD_MOSI", ["sd_MOSI"]),  # pin 3 on micro SD, 2 on full SD
        Pin(2, "CD_DAT3_CS", ["sd_nSS"]),  # pin 2 on micro SD, 1 on full SD
        Pin(1, "DAT2"),  # pin 1 on micro SD, 9 on full SD
        Pin("SH1", "GND"),
        Pin("SH2", "GND"),
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    identifier="EXTSD",
    value="ext sd",
    pins=[
        Pin(1, "1", ["sd_nSS"]),
        Pin(2, "2", ["sd_MOSI"]),
        Pin(3, "3", ["3V3"]),
        Pin(4, "4", ["sd_SCK"]),
        Pin(5, "5", ["GND"]),
        Pin(6, "6", ["sd_MISO"]),
    ],
)

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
